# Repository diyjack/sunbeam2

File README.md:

##Sunbeam2.0
==========

##What is it?
Just a smoothieboard based electronics that im developing.

## Licensing
==========

Copyright (C) 2012 Arkadiusz Spiewak (Wulfnor)

licensed under the GPL license: [http://www.gnu.org/licenses/gpl.html](http://www.gnu.org/licenses/gpl.html)
license.txt file included.

##Author
Author is: Arkadiusz Spiewak a'ka Wulfnor

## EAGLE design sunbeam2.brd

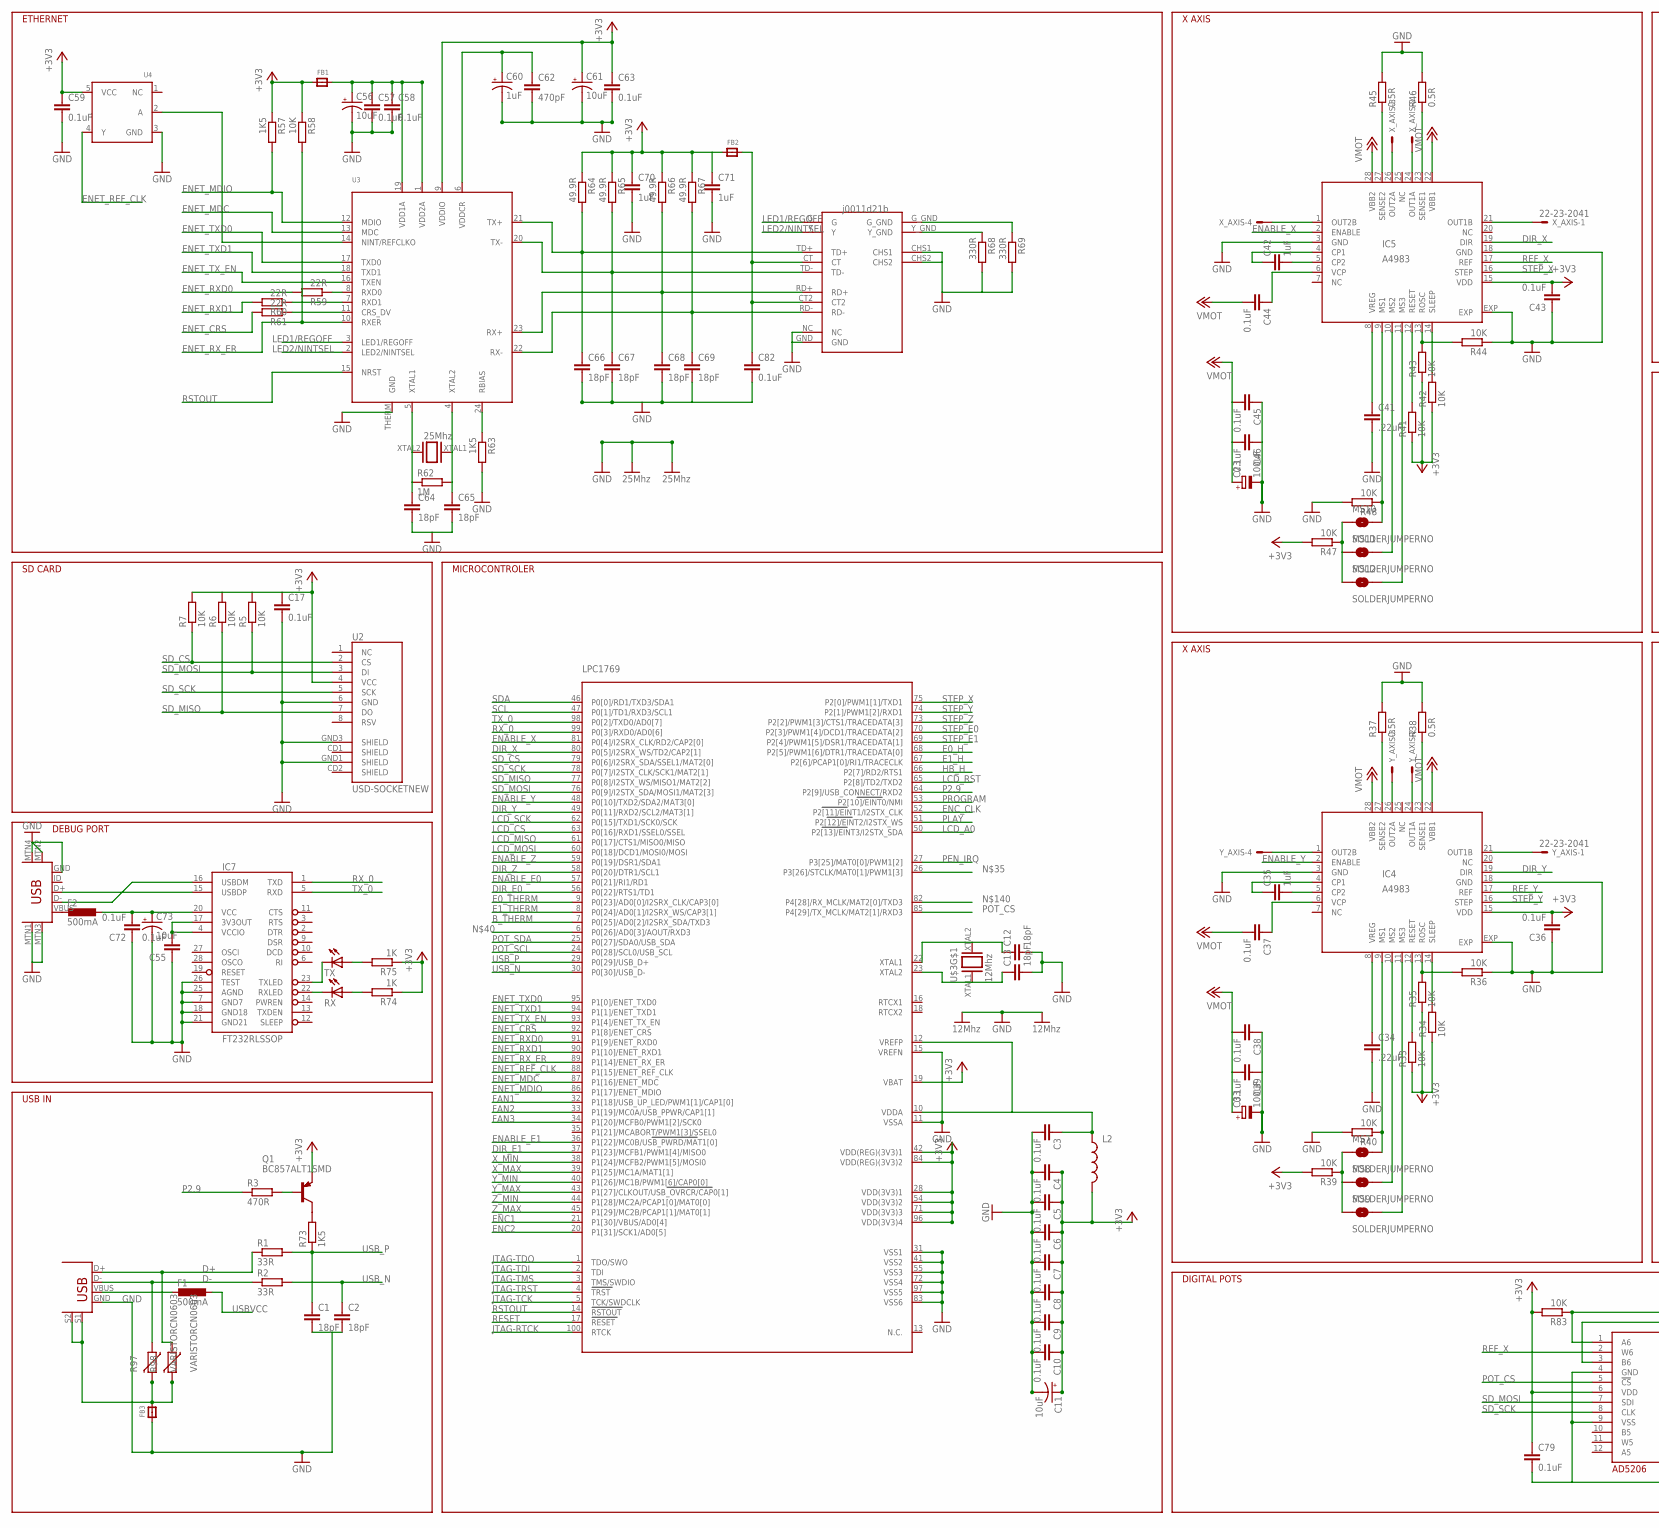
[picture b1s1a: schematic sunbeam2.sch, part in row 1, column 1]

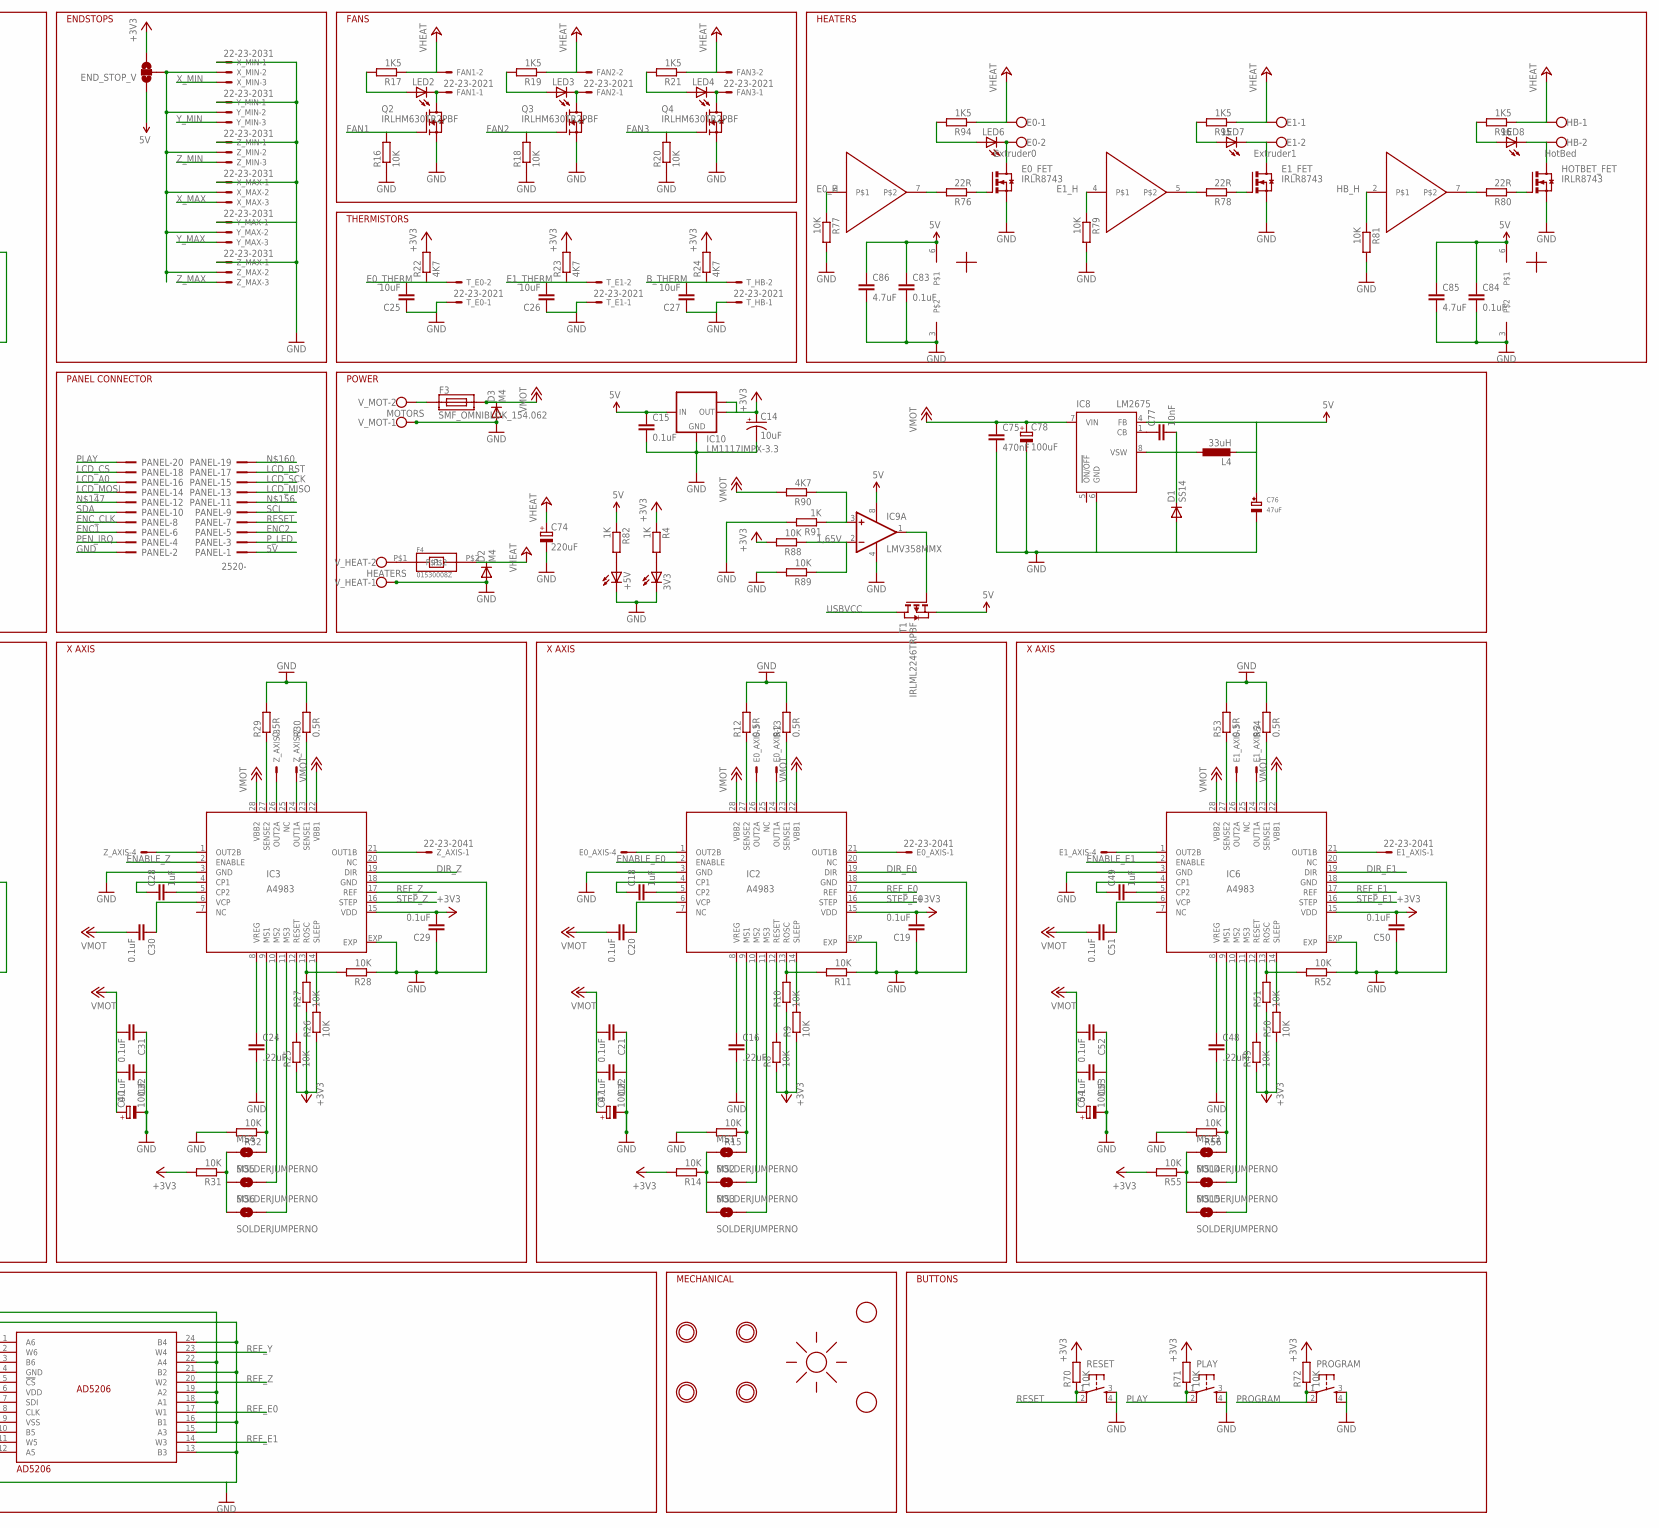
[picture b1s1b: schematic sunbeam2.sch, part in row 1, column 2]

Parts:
3V3: LEDCHIPLED_0805; CHIPLED_0805
+5V: LEDCHIPLED_0805; CHIPLED_0805
AD5206: AD5206; TSSOP24
C1, C2, C12, C13, C64, C65, C66, C67, C68, C69: 18pF; C0603
C3, C4, C5, C6, C7, C8, C9, C10, C17, C19, C29, C36, C43, C50, C55, C57, C58, C59, C63, C72, C79, C82, C83, C84: 0.1uF; C0603
C11, C14, C56, C61, C73: 10uF; EIA3216
C15, C20, C21, C22, C30, C31, C32, C37, C38, C39, C44, C45, C46, C51, C52, C53: 0.1uF; C0805
C16, C24, C34, C41, C48: .22uF; C0603
C18, C28, C35, C42, C49, C70, C71: 1uF; C0603
C23, C33, C40, C47, C54: 100uF; UD-6,3X7,7_NICHICON
C25, C26, C27: 10uF; C0603
C60: 1uF; EIA3216
C62: 470pF; C0603
C74: 220uF; UD-8X10_NICHICON
C75: 470nF; C0805
C76: 47uF; EIA7343-31/D-R
C77: 10nF; C0805
C78: 100uF; UD-8X10_NICHICON
C85, C86: 4.7uF; C0603
D1: SS14; DO214AC
D2, D3: M4; DO214AC
E0: Extruder0; W237-102; MPN 237-102
E0_AXIS, E1_AXIS: 22-23-2041
E0_FET, E1_FET: IRLR8743; D-PAK_TO252AA
E1: Extruder1; W237-102; MPN 237-102
END_STOP_V: SOLDERJUMPER_2WAYS; SJ_3
F1, F2: 500mA; L1812
F3: SMF_OMNIBLOK_154.062; NANO2_SMF_FUSEBLOCK
F4: 01530008Z
FAN1, FAN2, FAN3: 22-23-2021
FB1, FB2, FB3: FERRITE_0603; _0603
FET_DRV1, FET_DRV2: TC4427; SOIC8
GND: MOUNTINGHOLE3.0THIN; MOUNTINGHOLE_3.0_PLATEDTHIN
HB: HotBed; W237-102; MPN 237-102
HOTBET_FET: IRLR8743; D-PAK_TO252AA
IC2, IC3, IC4, IC5, IC6: A4983; QFN28ET
IC7: FT232RLSSOP; SSOP28DB
IC8: LM2675; SO08
IC9: LMV358MMX; MSOP08
IC10: LM1117IMPX-3.3; SOT223
L2: INDUCTOR0603; 0603
L4: 33uH; PIS2816
LED2, LED3, LED4, LED6, LED7, LED8: LEDCHIPLED_0805; CHIPLED_0805
LPC1769: LPC1768; LQFP100
MS1, MS2, MS3, MS4, MS5, MS6, MS7, MS8, MS9, MS10, MS11, MS12, MS13, MS14, MS15: SOLDERJUMPERNO; SJ_2S-NO
PANEL: 2520-; PAK100/2500-20
PLAY: TAC_SWITCHSMD; TACTILE_SWITCH_SMD
PROGRAM: TAC_SWITCHSMD; TACTILE_SWITCH_SMD
Q1: BC857ALT1SMD; SOT23-BEC
Q2, Q3, Q4: IRLHM630TR2PBF; PQFN33
R1, R2: 33R; R0603
R3: 470R; R0603
R4, R74, R75, R82, R91: 1K; R0603
R5, R6, R7, R8, R9, R10, R11, R14, R15, R16, R18, R20, R25, R26, R27, R28, R31, R32, R33, R34, R35, R36, R39, R40, R41, R42, R43, R44, R47, R48, R49, R50, R51, R52, R55, R56, R58, R70, R71, R72, R77, R79, R81, R83, R88, R89: 10K; R0603
R12, R13, R29, R30, R37, R38, R45, R46, R53, R54: 0.5R; R2512
R17, R19, R21, R57, R63, R73, R94, R95, R96: 1K5; R0603
R22, R23, R24, R90: 4K7; R0603
R59, R60, R61, R76, R78, R80: 22R; R0603
R62: 1M; R0603
R64, R65, R66, R67: 49.9R; R0603
R68, R69: 330R; R0603
R97, R98: VARISTORCN0603; CT/CN0603
RESET: TAC_SWITCHSMD; TACTILE_SWITCH_SMD
RJ1: ETHERNET; J0011D21B
RX: LEDCHIPLED_0805; CHIPLED_0805
T1: IRLML2246TRPBF; SOT-23
TX: LEDCHIPLED_0805; CHIPLED_0805
T_E0, T_E1: 22-23-2021
T_HB: 22-23-2021
U2: USD-SOCKETNEW; MICRO-SD-SOCKET-PP
U3: LAN8720; QFN24_4MM
U4: 74LVC1G04; SOT23-5
U$1: USB+SHIELD; USB-B-PTH
U$3: 12Mhz; CRYSTAL2734
U$7: USB-MINIB-5PIN; USB-MINIB
U$8: 25Mhz; CRYSTAL2734
U$17, U$18, U$20: MOUNTINGHOLE3.0THIN; MOUNTINGHOLE_3.0_PLATEDTHIN
U$21: SUNLOGO; SUN
U$22, U$23: FIDUCIAL; FIDUCIAL_1MM
V_HEAT: HEATERS; W237-102
V_MOT: MOTORS; W237-102
X_AXIS: 22-23-2041
X_MAX: 22-23-2031; MPN 22-23-2031
X_MIN: 22-23-2031
Y_AXIS: 22-23-2041
Y_MAX: 22-23-2031; MPN 22-23-2031
Y_MIN: 22-23-2031
Z_AXIS: 22-23-2041
Z_MAX: 22-23-2031; MPN 22-23-2031
Z_MIN: 22-23-2031

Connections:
1,65V: IC9.2 (-IN), R88.1, R89.1
5V: C15.1, C76.+, C83.1, C84.1, C85.1, C86.1, END_STOP_V.1, FET_DRV1.6, FET_DRV2.6, IC8.4 (FB), IC9.8 (V+), IC10.3 (IN), L4.2, PANEL.1, R82.1, T1.2 (S)
+3V3: AD5206.6 (VDD), C4.1, C5.1, C6.1, C7.1, C8.1, C9.1, C10.1, C11.A (+), C14.A (+), C17.1, C19.2, C29.2, C36.2, C43.2, C50.2, C59.1, C61.A (+), C63.1, C70.1, C71.1, C79.1, END_STOP_V.3, FB1.1, FB2.1, IC2.15 (VDD), IC3.15 (VDD), IC4.15 (VDD), IC5.15 (VDD), IC6.15 (VDD), IC10.2 (OUT), IC10.TAB (OUT1), L2.2, LPC1769.19 (VBAT), LPC1769.28 (VDD(3V3)1), LPC1769.42 (VDD(REG)(3V3)1), LPC1769.54 (VDD(3V3)2), LPC1769.71 (VDD(3V3)3), LPC1769.84 (VDD(REG)(3V3)2), LPC1769.96 (VDD(3V3)4), Q1.E, R4.1, R5.2, R6.2, R7.2, R8.1, R9.1, R10.1, R14.2, R22.2, R23.2, R24.2, R25.1, R26.1, R27.1, R31.2, R33.1, R34.1, R35.1, R39.2, R41.1, R42.1, R43.1, R47.2, R49.1, R50.1, R51.1, R55.2, R57.1, R58.1, R64.1, R65.1, R66.1, R67.1, R70.2, R71.2, R72.2, R74.1, R75.1, R83.2, R88.2, U2.4 (VCC), U3.9 (VDDIO), U4.5 (VCC)
+12V: C20.2, C21.2, C22.2, C23.+, C30.2, C31.2, C32.2, C33.+, C37.2, C38.2, C39.2, C40.+, C44.2, C45.2, C46.2, C47.+, C51.2, C52.2, C53.2, C54.+, C75.1, C78.+, D3.C, F3.2, IC2.22 (VBB1), IC2.28 (VBB2), IC3.22 (VBB1), IC3.28 (VBB2), IC4.22 (VBB1), IC4.28 (VBB2), IC5.22 (VBB1), IC5.28 (VBB2), IC6.22 (VBB1), IC6.28 (VBB2), IC8.7 (VIN), R90.2
B_THERM: C27.2, LPC1769.7 (P0[25]/AD0[2]/I2SRX_SDA/TXD3), R24.1, T_HB.2
D+: R1.1, R98.1, U$1.D+
D-: R2.1, R97.1, U$1.D-
DIR_E0: IC2.19 (DIR), LPC1769.56 (P0[22]/RTS1/TD1)
DIR_E1: IC6.19 (DIR), LPC1769.37 (P1[23]/MCFB1/PWM1[4]/MISO0)
DIR_X: IC5.19 (DIR), LPC1769.80 (P0[5]/I2SRX_WS/TD2/CAP2[1])
DIR_Y: IC4.19 (DIR), LPC1769.49 (P0[11]/RXD2/SCL2/MAT3[1])
DIR_Z: IC3.19 (DIR), LPC1769.58 (P0[20]/DTR1/SCL1)
E0_H: FET_DRV1.2, LPC1769.68 (P2[5]/PWM1[6]/DTR1/TRACEDATA[0]), R77.1
E0_THERM: C25.2, LPC1769.9 (P0[23]/AD0[0]/I2SRX_CLK/CAP3[0]), R22.1, T_E0.2
E1_H: FET_DRV1.4, LPC1769.67 (P2[6]/PCAP1[0]/RI1/TRACECLK), R79.1
E1_THERM: C26.2, LPC1769.8 (P0[24]/AD0[1]/I2SRX_WS/CAP3[1]), R23.1, T_E1.2
ENABLE_E0: IC2.2 (ENABLE), LPC1769.57 (P0[21]/RI1/RD1)
ENABLE_E1: IC6.2 (ENABLE), LPC1769.36 (P1[22]/MC0B/USB_PWRD/MAT1[0])
ENABLE_X: IC5.2 (ENABLE), LPC1769.81 (P0[4]/I2SRX_CLK/RD2/CAP2[0])
ENABLE_Y: IC4.2 (ENABLE), LPC1769.48 (P0[10]/TXD2/SDA2/MAT3[0])
ENABLE_Z: IC3.2 (ENABLE), LPC1769.59 (P0[19]/DSR1/SDA1)
ENC1: LPC1769.21 (P1[30]/VBUS/AD0[4]), PANEL.6
ENC2: LPC1769.20 (P1[31]/SCK1/AD0[5]), PANEL.5
ENC_CLK: LPC1769.52 (P2[11]/EINT1/I2STX_CLK), PANEL.8
ENET_CRS: LPC1769.92 (P1[8]/ENET_CRS), R61.2
ENET_MDC: LPC1769.87 (P1[16]/ENET_MDC), U3.13 (MDC)
ENET_MDIO: LPC1769.86 (P1[17]/ENET_MDIO), R57.2, U3.12 (MDIO)
ENET_REF_CLK: LPC1769.88 (P1[15]/ENET_REF_CLK), U4.4 (Y)
ENET_RXD0: LPC1769.91 (P1[9]/ENET_RXD0), R59.2
ENET_RXD1: LPC1769.90 (P1[10]/ENET_RXD1), R60.2
ENET_RX_ER: LPC1769.89 (P1[14]/ENET_RX_ER), R58.2, U3.10 (RXER)
ENET_TXD0: LPC1769.95 (P1[0]/ENET_TXD0), U3.17 (TXD0)
ENET_TXD1: LPC1769.94 (P1[1]/ENET_TXD1), U3.18 (TXD1)
ENET_TX_EN: LPC1769.93 (P1[4]/ENET_TX_EN), U3.16 (TXEN)
FAN1: LPC1769.32 (P1[18]/USB_UP_LED/PWM1[1]/CAP1[0]), Q2.G, R16.2
FAN2: LPC1769.33 (P1[19]/MC0A/USB_PPWR/CAP1[1]), Q3.G, R18.2
FAN3: LPC1769.34 (P1[20]/MCFB0/PWM1[2]/SCK0), Q4.G, R20.2
GND: 3V3.C, +5V.C, AD5206.3 (B6), AD5206.4 (GND), AD5206.9 (VSS), AD5206.13 (B3), AD5206.16 (B1), AD5206.21 (B2), AD5206.24 (B4), C1.2, C2.2, C3.2, C4.2, C5.2, C6.2, C7.2, C8.2, C9.2, C10.2, C11.C (-), C12.2, C13.2, C14.C (-), C15.2, C16.2, C17.2, C19.1, C21.1, C22.1, C23.-, C24.2, C25.1, C26.1, C27.1, C29.1, C31.1, C32.1, C33.-, C34.2, C36.1, C38.1, C39.1, C40.-, C41.2, C43.1, C45.1, C46.1, C47.-, C48.2, C50.1, C52.1, C53.1, C54.-, C55.1, C56.C (-), C57.2, C58.2, C59.2, C60.C (-), C61.C (-), C62.2, C63.2, C64.2, C65.2, C66.2, C67.2, C68.2, C69.2, C70.2, C71.2, C72.1, C73.C (-), C74.-, C75.2, C76.-, C78.-, C79.2, C82.2, C83.2, C84.2, C85.2, C86.2, D1.A, D2.A, D3.A, E0_FET.3 (S), E1_FET.3 (S), FB3.1, FET_DRV1.3, FET_DRV2.3, HOTBET_FET.3 (S), IC2.3 (GND), IC2.18 (GND), IC2.EXP, IC3.3 (GND), IC3.18 (GND), IC3.EXP, IC4.3 (GND), IC4.18 (GND), IC4.EXP, IC5.3 (GND), IC5.18 (GND), IC5.EXP, IC6.3 (GND), IC6.18 (GND), IC6.EXP, IC7.7 (GND7), IC7.18 (GND18), IC7.21 (GND21), IC7.25 (AGND), IC7.26 (TEST), IC8.6 (GND), IC9.4 (V-), IC10.1 (GND), LPC1769.11 (VSSA), LPC1769.15 (VREFN), LPC1769.31 (VSS1), LPC1769.41 (VSS2), LPC1769.55 (VSS3), LPC1769.72 (VSS4), LPC1769.83 (VSS6), LPC1769.97 (VSS5), PANEL.2, PLAY.3, PLAY.4, PROGRAM.3, PROGRAM.4, Q2.S, Q3.S, Q4.S, R11.1, R12.2, R13.2, R15.2, R16.1, R18.1, R20.1, R28.1, R29.2, R30.2, R32.2, R36.1, R37.2, R38.2, R40.2, R44.1, R45.2, R46.2, R48.2, R52.1, R53.2, R54.2, R56.2, R63.2, R68.2, R69.2, R77.2, R79.2, R81.2, R89.2, R91.2, RESET.3, RESET.4, RJ1.CHS1, RJ1.CHS2, RJ1.GND, RJ1.NC, T_E0.1, T_E1.1, T_HB.1, U2.6 (GND), U2.GND1 (SHIELD), U2.GND3 (SHIELD), U3.THERM (GND), U4.3 (GND), U$1.GND, U$3.GND1 (GND), U$3.GND2 (GND), U$7.GND, U$7.MTN1 (MTN2), U$7.MTN2 (MTN3), U$7.MTN3 (MTN1), U$7.MTN4, U$8.GND1 (GND), U$8.GND2 (GND), V_HEAT.1, V_MOT.1, X_MAX.1, X_MIN.1, Y_MAX.1, Y_MIN.1, Z_MAX.1, Z_MIN.1
HB_H: FET_DRV2.2, LPC1769.66 (P2[7]/RD2/RTS1), R81.1
JTAG-RTCK: LPC1769.100 (RTCK)
JTAG-TCK: LPC1769.5 (TCK/SWDCLK)
JTAG-TDI: LPC1769.2 (TDI)
JTAG-TDO: LPC1769.1 (TDO/SWO)
JTAG-TMS: LPC1769.3 (TMS/SWDIO)
JTAG-TRST: LPC1769.4 (TRST)
LCD_A0: LPC1769.50 (P2[13]/EINT3/I2STX_SDA), PANEL.16
LCD_CS: LPC1769.63 (P0[16]/RXD1/SSEL0/SSEL), PANEL.18
LCD_MISO: LPC1769.61 (P0[17]/CTS1/MISO0/MISO), PANEL.13
LCD_MOSI: LPC1769.60 (P0[18]/DCD1/MOSI0/MOSI), PANEL.14
LCD_RST: LPC1769.65 (P2[8]/TD2/TXD2), PANEL.17
LCD_SCK: LPC1769.62 (P0[15]/TXD1/SCK0/SCK), PANEL.15
LED1/REGOFF: RJ1.G, U3.3 (LED1/REGOFF)
LED2/NINTSEL: RJ1.Y, U3.2 (LED2/NINTSEL)
unnamed: F1.2, U$1.VBUS
unnamed: Q1.B, R3.2
unnamed: FB3.2, R97.2, R98.2, U$1.S1, U$1.S2
unnamed: FAN1.1, LED2.C, Q2.D
unnamed: FAN2.1, LED3.C, Q3.D
unnamed: C13.1, LPC1769.23 (XTAL2), U$3.XTAL1 (1)
unnamed: C12.1, LPC1769.22 (XTAL1), U$3.XTAL2 (2)
unnamed: E0_AXIS.1, IC2.21 (OUT1B)
unnamed: E0_AXIS.2, IC2.24 (OUT1A)
unnamed: 3V3.A, R4.2
unnamed: C3.1, L2.1, LPC1769.10 (VDDA), LPC1769.12 (VREFP)
unnamed: E0_AXIS.3, IC2.26 (OUT2A)
unnamed: E0_AXIS.4, IC2.1 (OUT2B)
unnamed: IC2.12 (RESET), R8.2
unnamed: IC2.14 (SLEEP), R9.2
unnamed: IC2.13 (ROSC), R10.2, R11.2
unnamed: C16.1, IC2.8 (VREG)
unnamed: C18.2, IC2.5 (CP2)
unnamed: C18.1, IC2.4 (CP1)
unnamed: IC2.27 (SENSE2), R12.1
unnamed: IC2.23 (SENSE1), R13.1
unnamed: C20.1, IC2.6 (VCP)
unnamed: IC2.9 (MS1), MS1.2, R15.1
unnamed: IC2.10 (MS2), MS2.2
unnamed: IC2.11 (MS3), MS3.2
unnamed: MS1.1, MS2.1, MS3.1, R14.1
unnamed: F3.1, V_MOT.2
unnamed: HB.2, HOTBET_FET.4 (D), LED8.C
unnamed: E1.2, E1_FET.4 (D), LED7.C
unnamed: E0.2, E0_FET.4 (D), LED6.C
unnamed: E0_FET.1 (G), R76.1
unnamed: E1_FET.1 (G), R78.1
unnamed: FET_DRV1.7, R76.2
unnamed: LED6.A, R94.2
unnamed: Q1.C, R73.2
unnamed: IC3.21 (OUT1B), Z_AXIS.1
unnamed: IC3.24 (OUT1A), Z_AXIS.2
unnamed: IC3.26 (OUT2A), Z_AXIS.3
unnamed: IC3.1 (OUT2B), Z_AXIS.4
unnamed: LED3.A, R19.2
unnamed: END_STOP_V.2, X_MAX.2, X_MIN.2, Y_MAX.2, Y_MIN.2, Z_MAX.2, Z_MIN.2
unnamed: LED2.A, R17.2
unnamed: FAN3.1, LED4.C, Q4.D
unnamed: LED4.A, R21.2
unnamed: IC3.12 (RESET), R25.2
unnamed: IC3.14 (SLEEP), R26.2
unnamed: IC3.13 (ROSC), R27.2, R28.2
unnamed: C24.1, IC3.8 (VREG)
unnamed: C28.2, IC3.5 (CP2)
unnamed: C28.1, IC3.4 (CP1)
unnamed: IC3.27 (SENSE2), R29.1
unnamed: IC3.23 (SENSE1), R30.1
unnamed: C30.1, IC3.6 (VCP)
unnamed: IC3.9 (MS1), MS4.2, R32.1
unnamed: IC3.10 (MS2), MS5.2
unnamed: IC3.11 (MS3), MS6.2
unnamed: MS4.1, MS5.1, MS6.1, R31.1
unnamed: IC4.21 (OUT1B), Y_AXIS.1
unnamed: IC4.24 (OUT1A), Y_AXIS.2
unnamed: IC4.26 (OUT2A), Y_AXIS.3
unnamed: IC4.1 (OUT2B), Y_AXIS.4
unnamed: IC4.12 (RESET), R33.2
unnamed: IC4.14 (SLEEP), R34.2
unnamed: IC4.13 (ROSC), R35.2, R36.2
unnamed: C34.1, IC4.8 (VREG)
unnamed: C35.2, IC4.5 (CP2)
unnamed: C35.1, IC4.4 (CP1)
unnamed: IC4.27 (SENSE2), R37.1
unnamed: IC4.23 (SENSE1), R38.1
unnamed: C37.1, IC4.6 (VCP)
unnamed: IC4.9 (MS1), MS7.2, R40.1
unnamed: IC4.10 (MS2), MS8.2
unnamed: IC4.11 (MS3), MS9.2
unnamed: MS7.1, MS8.1, MS9.1, R39.1
unnamed: IC5.21 (OUT1B), X_AXIS.1
unnamed: IC5.24 (OUT1A), X_AXIS.2
unnamed: IC5.26 (OUT2A), X_AXIS.3
unnamed: IC5.1 (OUT2B), X_AXIS.4
unnamed: IC5.12 (RESET), R41.2
unnamed: IC5.14 (SLEEP), R42.2
unnamed: IC5.13 (ROSC), R43.2, R44.2
unnamed: C41.1, IC5.8 (VREG)
unnamed: C42.2, IC5.5 (CP2)
unnamed: C42.1, IC5.4 (CP1)
unnamed: IC5.27 (SENSE2), R45.1
unnamed: IC5.23 (SENSE1), R46.1
unnamed: C44.1, IC5.6 (VCP)
unnamed: IC5.9 (MS1), MS10.2, R48.1
unnamed: IC5.10 (MS2), MS11.2
unnamed: IC5.11 (MS3), MS12.2
unnamed: MS10.1, MS11.1, MS12.1, R47.1
unnamed: E1_AXIS.1, IC6.21 (OUT1B)
unnamed: E1_AXIS.2, IC6.24 (OUT1A)
unnamed: E1_AXIS.3, IC6.26 (OUT2A)
unnamed: E1_AXIS.4, IC6.1 (OUT2B)
unnamed: IC6.12 (RESET), R49.2
unnamed: IC6.14 (SLEEP), R50.2
unnamed: IC6.13 (ROSC), R51.2, R52.2
unnamed: C48.1, IC6.8 (VREG)
unnamed: C49.2, IC6.5 (CP2)
unnamed: C49.1, IC6.4 (CP1)
unnamed: IC6.27 (SENSE2), R53.1
unnamed: IC6.23 (SENSE1), R54.1
unnamed: C51.1, IC6.6 (VCP)
unnamed: IC6.9 (MS1), MS13.2, R56.1
unnamed: IC6.10 (MS2), MS14.2
unnamed: IC6.11 (MS3), MS15.2
unnamed: MS13.1, MS14.1, MS15.1, R55.1
unnamed: F2.2, U$7.VBUS
unnamed: IC7.15 (USBDP), U$7.D+
unnamed: IC7.16 (USBDM), U$7.D-
unnamed: C72.2, C73.A (+), F2.1, IC7.20 (VCC)
unnamed: C55.2, IC7.4 (VCCIO), IC7.17 (3V3OUT)
unnamed: IC7.22 (RXLED), RX.C
unnamed: F4.P$1, V_HEAT.2
unnamed: C56.A (+), C57.1, C58.1, FB1.2, U3.1 (VDD2A), U3.19 (VDD1A)
unnamed: R63.1, U3.24 (RBIAS)
unnamed: R74.2, RX.A
unnamed: U3.14 (NINT/REFCLKO), U4.2 (A)
unnamed: R59.1, U3.8 (RXD0)
unnamed: R60.1, U3.7 (RXD1)
unnamed: R61.1, U3.11 (CRS_DV)
unnamed: C65.1, R62.2, U3.4 (XTAL2), U$8.XTAL1 (1)
unnamed: C66.1, R64.2, RJ1.TD+, U3.21 (TX+)
unnamed: C60.A (+), C62.1, U3.6 (VDDCR)
unnamed: C64.1, R62.1, U3.5 (XTAL1), U$8.XTAL2 (2)
unnamed: C67.1, R65.2, RJ1.TD-, U3.20 (TX-)
unnamed: IC7.23 (TXLED), TX.C
unnamed: R75.2, TX.A
unnamed: FET_DRV1.5, R78.2
unnamed: C77.2, D1.C, IC8.8 (VSW), L4.1
unnamed: +5V.A, R82.2
unnamed: HOTBET_FET.1 (G), R80.1
unnamed: FET_DRV2.7, R80.2
unnamed: C69.1, R67.2, RJ1.RD-, U3.22 (RX-)
unnamed: LED7.A, R95.2
unnamed: C77.1, IC8.1 (CB)
unnamed: LED8.A, R96.2
unnamed: C68.1, R66.2, RJ1.RD+, U3.23 (RX+)
unnamed: AD5206.1 (A6), AD5206.15 (A3), AD5206.18 (A1), AD5206.19 (A2), AD5206.22 (A4), R83.1
unnamed: R68.1, RJ1.Y_GND
unnamed: R69.1, RJ1.G_GND
unnamed: C82.1, FB2.2, RJ1.CT, RJ1.CT2
unnamed: IC9.1 (OUT), T1.3 (G)
unnamed: IC9.3 (+IN), R90.1, R91.1
P2.9: LPC1769.64 (P2[9]/USB_CONNECT/RXD2), R3.1
PEN_IRQ: LPC1769.27 (P3[25]/MAT0[0]/PWM1[2]), PANEL.4
PLAY: LPC1769.51 (P2[12]/EINT2/I2STX_WS), PANEL.20, PLAY.1, PLAY.2, R71.1
POT_CS: AD5206.5 (!CS), LPC1769.85 (P4[29]/TX_MCLK/MAT2[1]/RXD3)
POT_SCL: LPC1769.24 (P0[28]/SCL0/USB_SCL)
POT_SDA: LPC1769.25 (P0[27]/SDA0/USB_SDA)
PROGRAM: LPC1769.53 (P2[10]/EINT0/NMI), PROGRAM.1, PROGRAM.2, R72.1
P_LED: PANEL.3
REF_E0: AD5206.17 (W1), IC2.17 (REF)
REF_E1: AD5206.14 (W3), IC6.17 (REF)
REF_X: AD5206.2 (W6), IC5.17 (REF)
REF_Y: AD5206.23 (W4), IC4.17 (REF)
REF_Z: AD5206.20 (W2), IC3.17 (REF)
RESET: LPC1769.17 (RESET), PANEL.7, R70.1, RESET.1, RESET.2
RSTOUT: LPC1769.14 (RSTOUT), U3.15 (NRST)
RX_0: IC7.1 (TXD), LPC1769.99 (P0[3]/RXD0/AD0[6])
SCL: LPC1769.47 (P0[1]/TD1/RXD3/SCL1), PANEL.9
SDA: LPC1769.46 (P0[0]/RD1/TXD3/SDA1), PANEL.10
SD_CS: LPC1769.79 (P0[6]/I2SRX_SDA/SSEL1/MAT2[0]), R7.1, U2.2 (CS)
SD_MISO: LPC1769.77 (P0[8]/I2STX_WS/MISO1/MAT2[2]), R6.1, U2.7 (DO)
SD_MOSI: AD5206.7 (SDI), LPC1769.76 (P0[9]/I2STX_SDA/MOSI1/MAT2[3]), R5.1, U2.3 (DI)
SD_SCK: AD5206.8 (CLK), LPC1769.78 (P0[7]/I2STX_CLK/SCK1/MAT2[1]), U2.5 (SCK)
STEP_E0: IC2.16 (STEP), LPC1769.70 (P2[3]/PWM1[4]/DCD1/TRACEDATA[2])
STEP_E1: IC6.16 (STEP), LPC1769.69 (P2[4]/PWM1[5]/DSR1/TRACEDATA[1])
STEP_X: IC5.16 (STEP), LPC1769.75 (P2[0]/PWM1[1]/TXD1)
STEP_Y: IC4.16 (STEP), LPC1769.74 (P2[1]/PWM1[2]/RXD1)
STEP_Z: IC3.16 (STEP), LPC1769.73 (P2[2]/PWM1[3]/CTS1/TRACEDATA[3])
TX_0: IC7.5 (RXD), LPC1769.98 (P0[2]/TXD0/AD0[7])
USBVCC: F1.1, T1.1 (D)
USB_N: C2.1, LPC1769.30 (P0[30]/USB_D-), R2.2
USB_P: C1.1, LPC1769.29 (P0[29]/USB_D+), R1.2, R73.1
V_EXTR: C74.+, D2.C, E0.1, E1.1, F4.P$2, FAN1.2, FAN2.2, FAN3.2, HB.1, R17.1, R19.1, R21.1, R94.1, R95.1, R96.1
X_MAX: LPC1769.39 (P1[25]/MC1A/MAT1[1]), X_MAX.3
X_MIN: LPC1769.38 (P1[24]/MCFB2/PWM1[5]/MOSI0), X_MIN.3
Y_MAX: LPC1769.43 (P1[27]/CLKOUT/USB_OVRCR/CAP0[1]), Y_MAX.3
Y_MIN: LPC1769.40 (P1[26]/MC1B/PWM1[6]/CAP0[0]), Y_MIN.3
Z_MAX: LPC1769.45 (P1[29]/MC2B/PCAP1[1]/MAT0[1]), Z_MAX.3
Z_MIN: LPC1769.44 (P1[28]/MC2A/PCAP1[0]/MAT0[0]), Z_MIN.3

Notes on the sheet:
USB IN
POWER
SD CARD
ETHERNET
ENDSTOPS
FANS
THERMISTORS
PANEL CONNECTOR
HEATERS
DEBUG PORT
X AXIS
MICROCONTROLER
DIGITAL POTS
MECHANICAL
BUTTONS

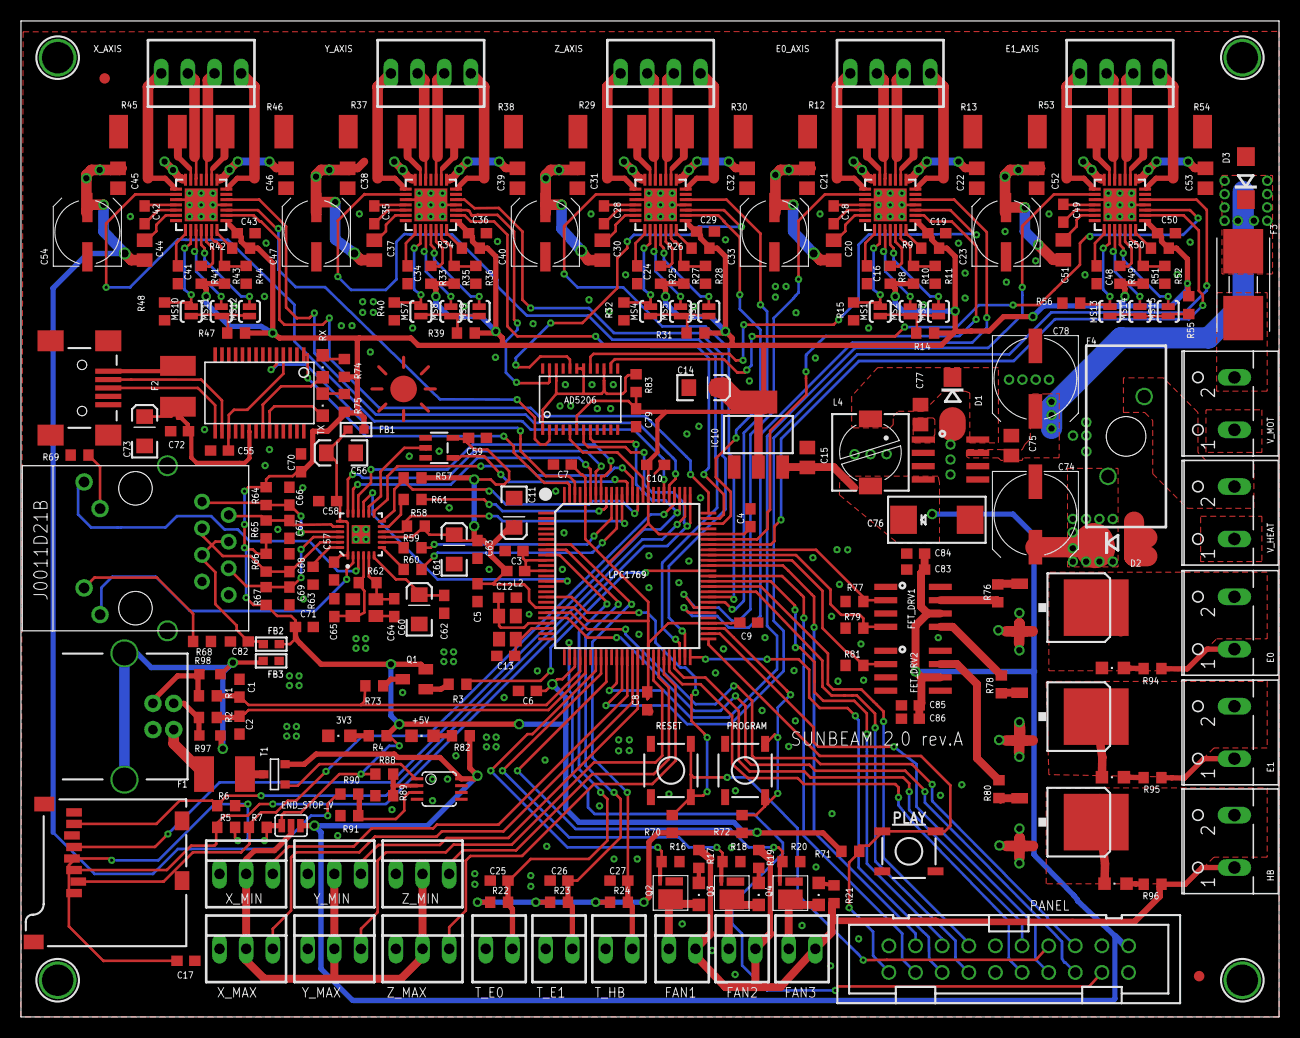
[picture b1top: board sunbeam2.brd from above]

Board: 2 copper layers, 120.0 x 95.0 mm, 276 parts (0 on the bottom side), 227 nets.

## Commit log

2013-01-03 readme file
2013-01-03 licence update to gpl
2013-01-05 -changed 3 2 channel pots to one 6 channel -moved play button -added fet driver for heater instead of bjts -changed some polygons [thanks triffin_hunter]
2013-01-09 -changed heaters fuse -some slight component changes
2013-01-09 -first BOM
2013-01-10 nothing important
2013-01-30 added paste layer for tranzistors

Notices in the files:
parts and their libraries:
SparkFun: Licensing: CC v3.0 Share-Alike You are welcome to use this library for commercial purposes.
microbuilder: This work is placed in the public domain, and may be freely used for commercial and non-commercial work with the following conditions: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
